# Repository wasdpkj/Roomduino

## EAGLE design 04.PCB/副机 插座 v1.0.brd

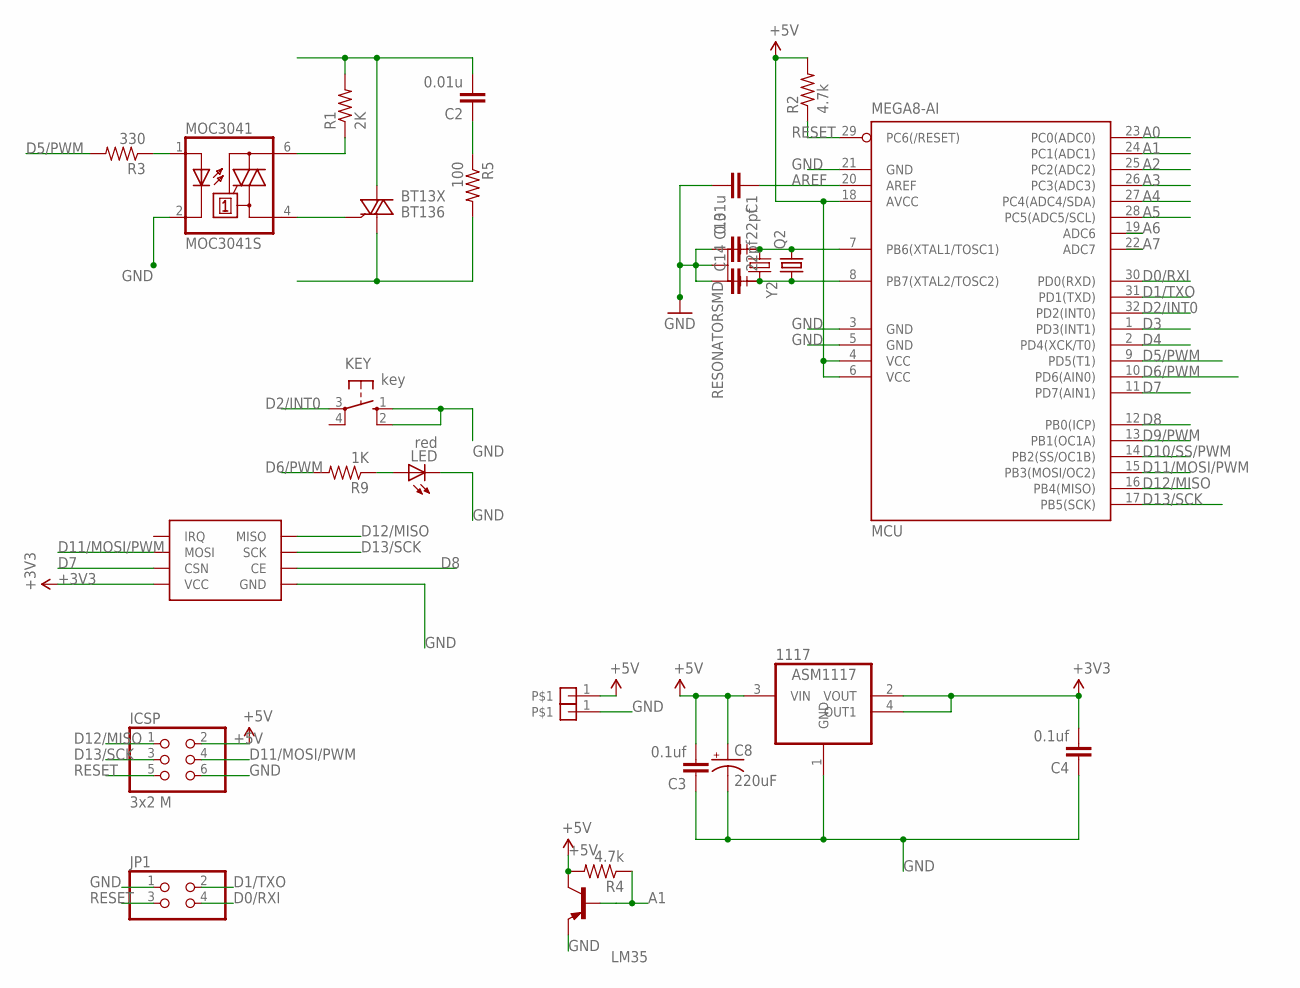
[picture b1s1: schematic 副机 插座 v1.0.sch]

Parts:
1117: ASM1117; SOT223
BT13X: BT136; TO252
C1: 0.01u; 0603-CAP
C2: 0.01u; C050-024X044
C3, C4: 0.1uf; 0603-CAP
C8: 220uF; EIA3528
C13, C14: 22pf; 0603-CAP
ICSP: 3x2 M; 2X03
JP1: PINHD-2X2; 2X02
KEY: key; B3F-10XX; MPN B3F-1000
LED: red; LED3MM
LM35: -PNP-TO92-E1; TO92-E1
MCU: MEGA8-AI; TQFP32-08
MOC3041: MOC3041S; DIL6-SMD; MPN MOC3041S-M
Q2: CRYSTALHC49S; HC49/S
R1: 2K; AXIAL-0.3
R2, R4: 4.7k; 0603-RES
R3: 330; 0603-RES
R5: 100; AXIAL-0.3
R9: 1K; 0603-RES
U$3, U$4: PIN1
U$6: NRF
Y2: RESONATORSMD; RESONATOR-SMD

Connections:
+3V3: 1117.2 (VOUT), 1117.4 (OUT1), C4.2, U$6.P$2 (VCC)
+5V: 1117.3 (VIN), C3.2, C8.A (+), ICSP.2, LM35.1 (C), MCU.4 (VCC), MCU.6 (VCC), MCU.18 (AVCC), R2.2, R4.2, U$3.1
A0: MCU.23 (PC0(ADC0))
A1: LM35.2 (B), MCU.24 (PC1(ADC1)), R4.1
A2: MCU.25 (PC2(ADC2))
A3: MCU.26 (PC3(ADC3))
A4: MCU.27 (PC4(ADC4/SDA))
A5: MCU.28 (PC5(ADC5/SCL))
A6: MCU.19 (ADC6)
A7: MCU.22 (ADC7)
AREF: C1.1, MCU.20 (AREF)
D0/RXI: JP1.4, MCU.30 (PD0(RXD))
D1/TXO: JP1.2, MCU.31 (PD1(TXD))
D2/INT0: KEY.3, MCU.32 (PD2(INT0))
D3: MCU.1 (PD3(INT1))
D4: MCU.2 (PD4(XCK/T0))
D5/PWM: MCU.9 (PD5(T1)), R3.2
D6/PWM: MCU.10 (PD6(AIN0)), R9.2
D7: MCU.11 (PD7(AIN1)), U$6.P$4 (CSN)
D8: MCU.12 (PB0(ICP)), U$6.P$3 (CE)
D9/PWM: MCU.13 (PB1(OC1A))
D10/SS/PWM: MCU.14 (PB2(SS/OC1B))
D11/MOSI/PWM: ICSP.4, MCU.15 (PB3(MOSI/OC2)), U$6.P$6 (MOSI)
D12/MISO: ICSP.1, MCU.16 (PB4(MISO)), U$6.P$7 (MISO)
D13/SCK: ICSP.3, MCU.17 (PB5(SCK)), U$6.P$5 (SCK)
GND: 1117.1 (GND), C1.2, C3.1, C4.1, C8.C (-), C13.1, C14.1, ICSP.6, JP1.1, KEY.1 (S), KEY.2 (S1), LED.K (C), LM35.3 (E), MCU.3 (GND), MCU.5 (GND), MCU.21 (GND), MOC3041.2 (C), U$4.1, U$6.P$1 (GND), Y2.2
IN: BT13X.3 (A2), C2.2, R1.P$2 (2)
unnamed: MOC3041.6 (A2), R1.P$1 (1)
unnamed: BT13X.2 (G), MOC3041.4 (A1)
unnamed: C2.1, R5.P$1 (1)
unnamed: LED.A, R9.1
unnamed: C13.2, MCU.7 (PB6(XTAL1/TOSC1)), Q2.2, Y2.1
unnamed: C14.2, MCU.8 (PB7(XTAL2/TOSC2)), Q2.1, Y2.3
OUT: BT13X.1 (A1), R5.P$2 (2)
P1: MOC3041.1 (A), R3.1
RESET: ICSP.5, JP1.3, MCU.29 (PC6(/RESET)), R2.1

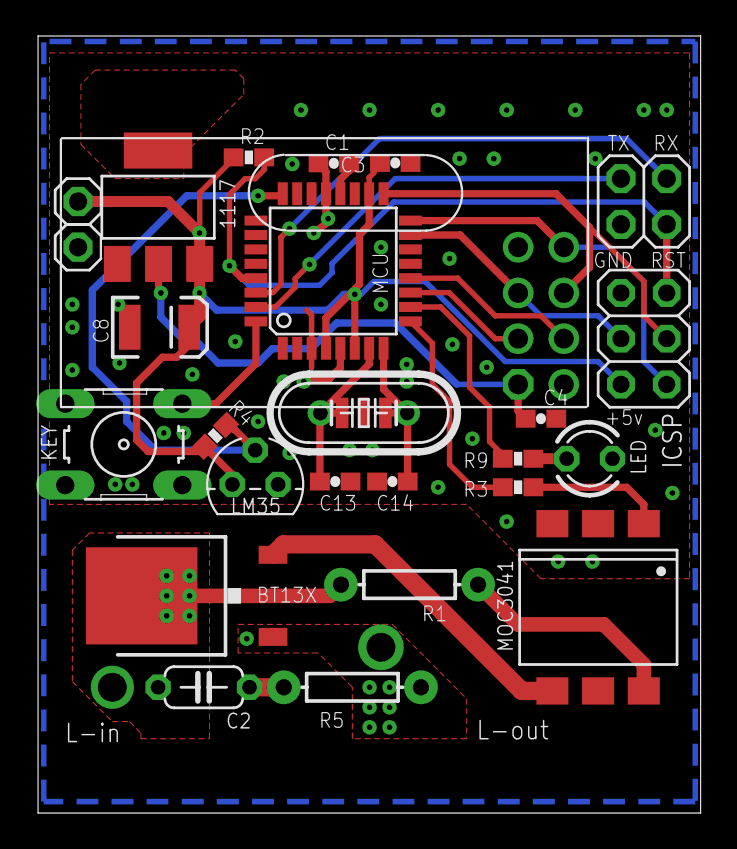
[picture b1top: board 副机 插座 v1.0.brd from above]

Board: 2 copper layers, 36.8 x 43.2 mm, 27 parts (0 on the bottom side), 25 nets.

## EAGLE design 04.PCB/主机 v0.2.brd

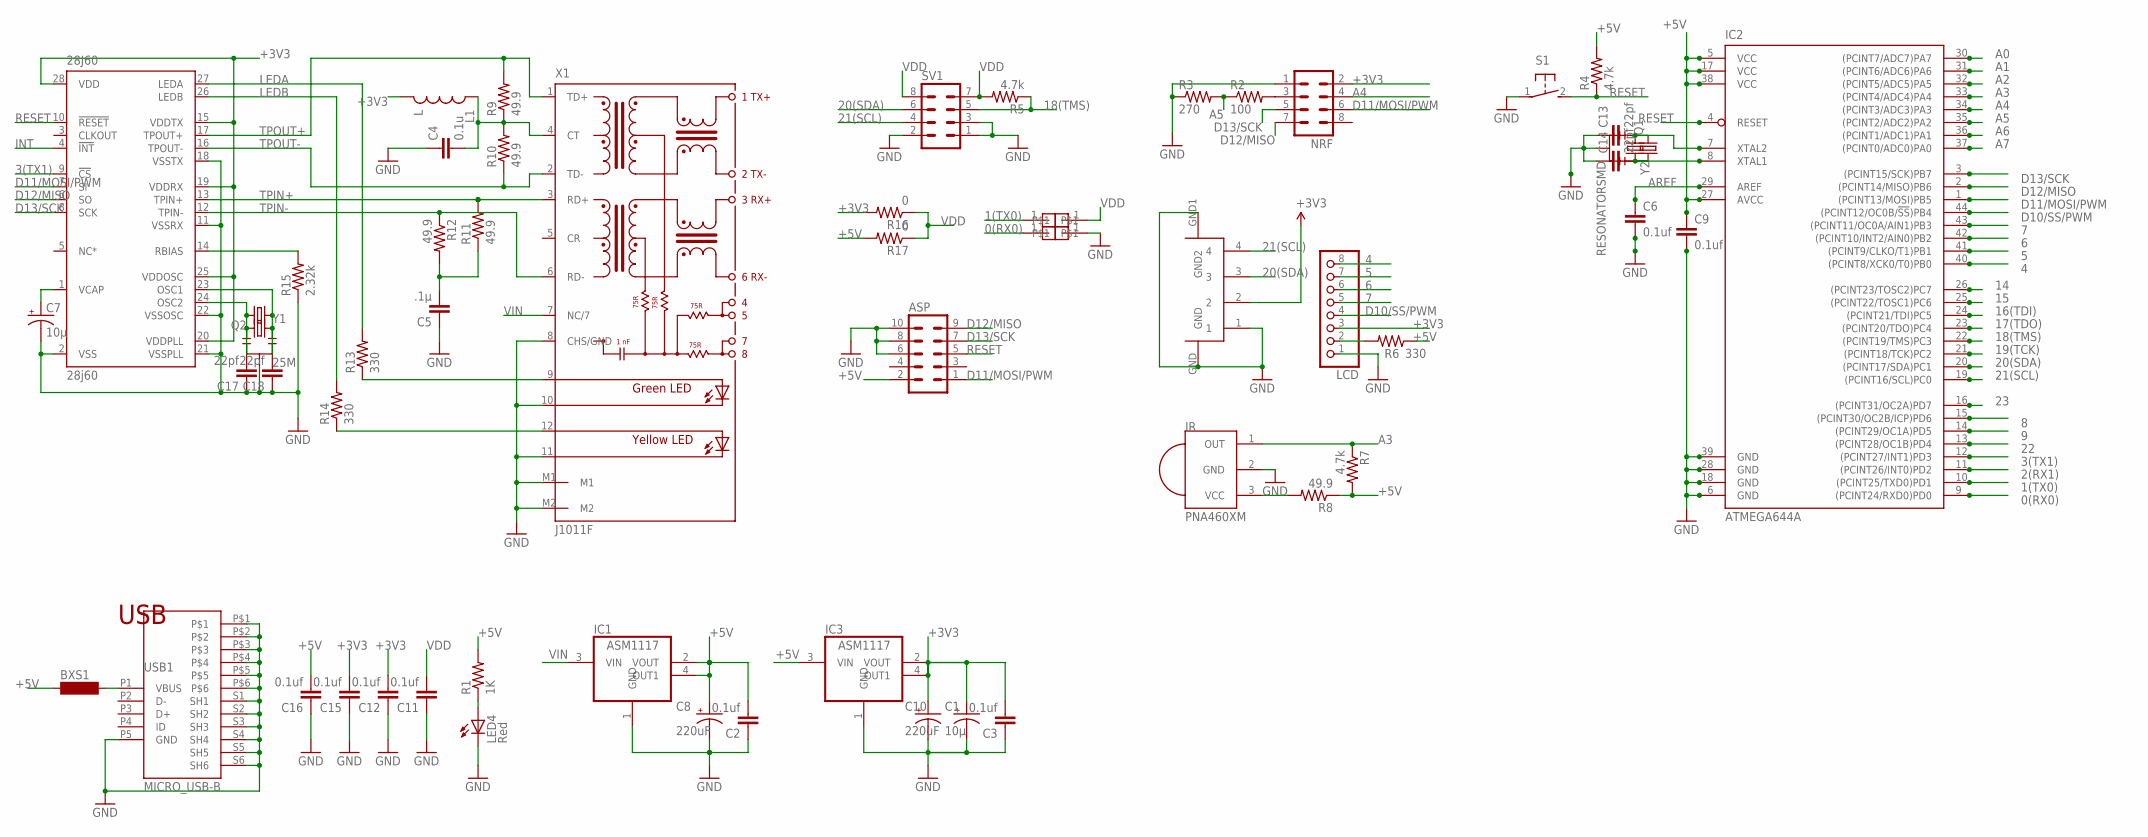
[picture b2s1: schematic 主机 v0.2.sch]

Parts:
28J60: 28j60; SSOP28DB
ASP: MA05-2
BXS1: SM-1206
C1, C7: 10µ; EIA3528
C2, C3, C6, C9, C11, C12, C15, C16: 0.1uf; 0603-CAP
C4: 0.1u; 0603-CAP
C5: .1µ; 0603-CAP
C8, C10: 220uF; 153CLV-0605
C13, C14, C17, C18: 22pf; 0603-CAP
IC1: ASM1117; SOT223
IC2: ATMEGA644A; TQFP44
IC3: ASM1117; SOT223; MPN REG1117
IR: PNA460XM
L1: L; 0603
LCD: PINHD-1X8; 1X08
LED4: Red; 0805-LED
NRF: MA04-2
Q1, Q2: CRYSTALHC49S; HC49/S
R1: 1K; 0603-RES
R2: 100; 0603-RES
R3: 270; 0603-RES
R4, R5, R7: 4.7k; 0603-RES
R6, R13, R14: 330; 0603-RES
R8, R9, R10, R11, R12: 49.9; 0603-RES
R15: 2.32k; 0603-RES
R16, R17: 0; 0603-RES
S1: 31-XX; B3F-31XX
SV1: MA04-2
U$2: S4B-XH-SM4-TB; XH-SM4-TB
U$4, U$5, U$6, U$7: PIN1
USB1: MICRO_USB-B; USB_MICRO_B
X1: J1011F; HRJ
Y1: 25M; RESONATOR-SMD
Y2: RESONATORSMD; RESONATOR-SMD

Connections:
0(RX0): IC2.9 ((PCINT24/RXD0)PD0), U$7.1
1(TX0): IC2.10 ((PCINT25/TXD0)PD1), U$6.1
2(RX1): IC2.11 ((PCINT26/INT0)PD2)
3(TX1): 28J60.9 (!CS), IC2.12 ((PCINT27/INT1)PD3)
4: IC2.40 ((PCINT8/XCK0/T0)PB0), LCD.8
5: IC2.41 ((PCINT9/CLKO/T1)PB1), LCD.7
6: IC2.42 ((PCINT10/INT2/AIN0)PB2), LCD.6
7: IC2.43 ((PCINT11/OC0A/AIN1)PB3), LCD.5
8: IC2.15 ((PCINT30/OC2B/ICP)PD6)
9: IC2.14 ((PCINT29/OC1A)PD5)
14: IC2.26 ((PCINT23/TOSC2)PC7)
15: IC2.25 ((PCINT22/TOSC1)PC6)
16(TDI): IC2.24 ((PCINT21/TDI)PC5)
17(TDO): IC2.23 ((PCINT20/TDO)PC4)
18(TMS): IC2.22 ((PCINT19/TMS)PC3), R5.1, SV1.5
19(TCK): IC2.21 ((PCINT18/TCK)PC2)
20(SDA): IC2.20 ((PCINT17/SDA)PC1), SV1.6, U$2.3
21(SCL): IC2.19 ((PCINT16/SCL)PC0), SV1.4, U$2.4
22: IC2.13 ((PCINT28/OC1B)PD4)
23: IC2.16 ((PCINT31/OC2A)PD7)
+3V3: 28J60.15 (VDDTX), 28J60.19 (VDDRX), 28J60.20 (VDDPLL), 28J60.25 (VDDOSC), 28J60.28 (VDD), C1.A (+), C3.2, C10.+, C12.2, C15.2, IC3.2 (VOUT), IC3.4 (OUT1), L1.2, LCD.3, NRF.2, R16.2, U$2.2
+5V: ASP.2, BXS1.1, C2.2, C8.+, C9.1, C16.2, IC1.2 (VOUT), IC1.4 (OUT1), IC2.5 (VCC), IC2.17 (VCC), IC2.27 (AVCC), IC2.38 (VCC), IC3.3 (VIN), R1.2, R4.2, R6.1, R7.2, R8.1, R17.2
A0: IC2.30 ((PCINT7/ADC7)PA7)
A1: IC2.31 ((PCINT6/ADC6)PA6)
A2: IC2.32 ((PCINT5/ADC5)PA5)
A3: IC2.33 ((PCINT4/ADC4)PA4), IR.1 (OUT), R7.1
A4: IC2.34 ((PCINT3/ADC3)PA3), NRF.4
A5: IC2.35 ((PCINT2/ADC2)PA2), R2.1, R3.2
A6: IC2.36 ((PCINT1/ADC1)PA1)
A7: IC2.37 ((PCINT0/ADC0)PA0)
AREF: C6.1, IC2.29 (AREF)
D10/SS/PWM: IC2.44 ((PCINT12/OC0B/!SS!)PB4), LCD.4
D11/MOSI/PWM: 28J60.7 (SI), ASP.1, IC2.1 ((PCINT13/MOSI)PB5), NRF.6
D12/MISO: 28J60.6 (SO), ASP.9, IC2.2 ((PCINT14/MISO)PB6), NRF.7
D13/SCK: 28J60.8 (SCK), ASP.7, IC2.3 ((PCINT15/SCK)PB7), NRF.5
GND: 28J60.2 (VSS), 28J60.11 (VSSRX), 28J60.18 (VSSTX), 28J60.21 (VSSPLL), 28J60.22 (VSSOSC), ASP.6, ASP.8, ASP.10, C1.C (-), C2.1, C3.1, C4.1, C5.1, C6.2, C7.C (-), C8.-, C9.2, C10.-, C11.1, C12.1, C13.1, C14.1, C15.1, C16.1, C17.1, C18.1, IC1.1 (GND), IC2.6 (GND), IC2.18 (GND), IC2.28 (GND), IC2.39 (GND), IC3.1 (GND), IR.2 (GND), LCD.1, LED4.C, NRF.1, R3.1, R15.1, S1.1, SV1.1, SV1.2, SV1.3, U$2.1, U$2.GND, U$2.GND1 (GND2), U$4.1, USB1.P5 (GND), USB1.P$1, USB1.P$2, USB1.P$3, USB1.P$4, USB1.P$5, USB1.P$6, USB1.S1 (SH1), USB1.S2 (SH2), USB1.S3 (SH3), USB1.S4 (SH4), USB1.S5 (SH5), USB1.S6 (SH6), X1.8 (CHS/GND), X1.10 (C-R), X1.11 (C-L), X1.M1, X1.M2, Y1.2, Y2.2
INT: 28J60.4 (!INT)
LEDA: 28J60.27 (LEDA), R13.2
LEDB: 28J60.26 (LEDB), R14.2
unnamed: C13.2, IC2.7 (XTAL2), Q1.2, Y2.1
unnamed: IR.3 (VCC), R8.2
unnamed: LED4.A, R1.1
unnamed: NRF.3, R2.2
unnamed: C5.2, R11.1, R12.2
unnamed: 28J60.1 (VCAP), C7.A (+)
unnamed: 28J60.14 (RBIAS), R15.2
unnamed: C14.2, IC2.8 (XTAL1), Q1.1, Y2.3
unnamed: C4.2, L1.1, R9.1, R10.2, X1.4 (CT)
unnamed: 28J60.24 (OSC2), C17.2, Q2.2, Y1.1
unnamed: 28J60.23 (OSC1), C18.2, Q2.1, Y1.3
unnamed: R13.1, X1.9 (A-R)
unnamed: R14.1, X1.12 (AL)
unnamed: LCD.2, R6.2
RESET: 28J60.10 (!RESET), ASP.5, IC2.4 (RESET), R4.1, S1.2 (S)
TPIN+: 28J60.13 (TPIN+), R11.2, X1.3 (RD+)
TPIN-: 28J60.12 (TPIN-), R12.1, X1.6 (RD-)
TPOUT+: 28J60.17 (TPOUT+), R9.2, X1.1 (TD+)
TPOUT-: 28J60.16 (TPOUT-), R10.1, X1.2 (TD-)
VDD: C11.2, R5.2, R16.1, R17.1, SV1.7, SV1.8, U$5.1
VIN: IC1.3 (VIN), X1.7 (NC/7)
VUSB: BXS1.2, USB1.P1 (VBUS)

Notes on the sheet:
USB

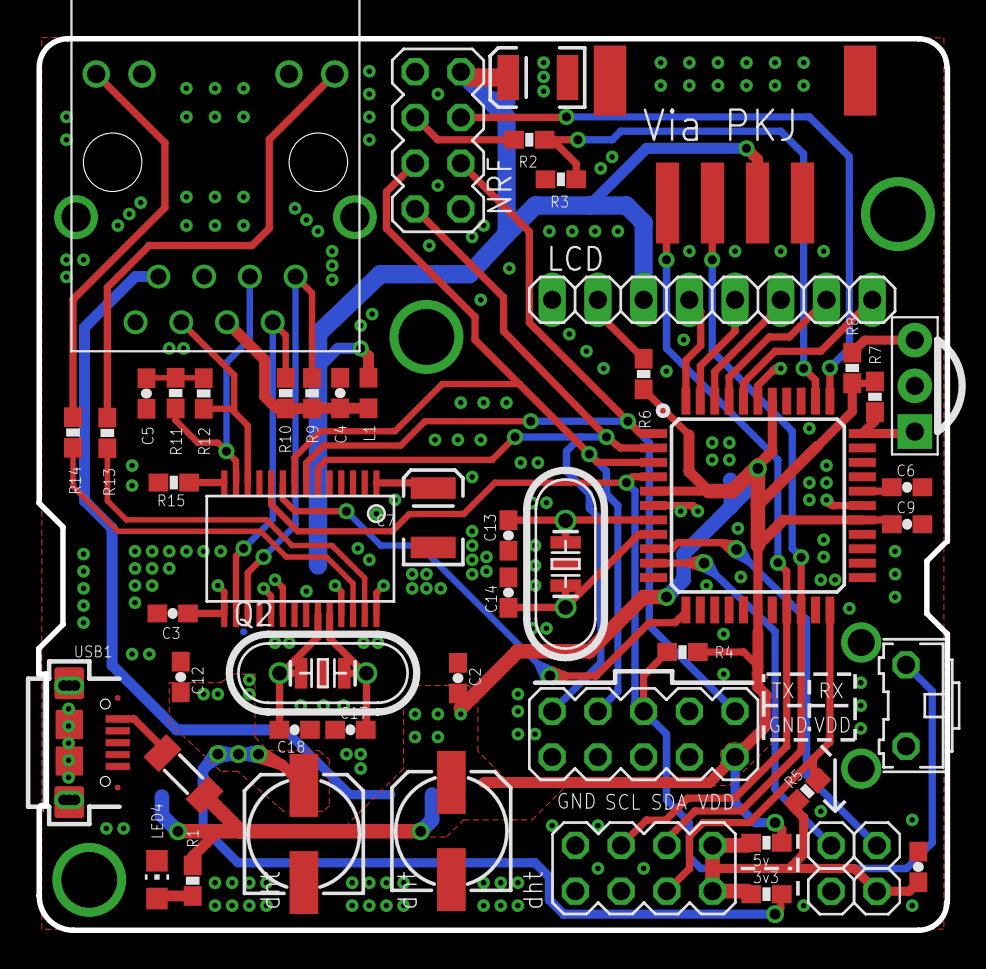
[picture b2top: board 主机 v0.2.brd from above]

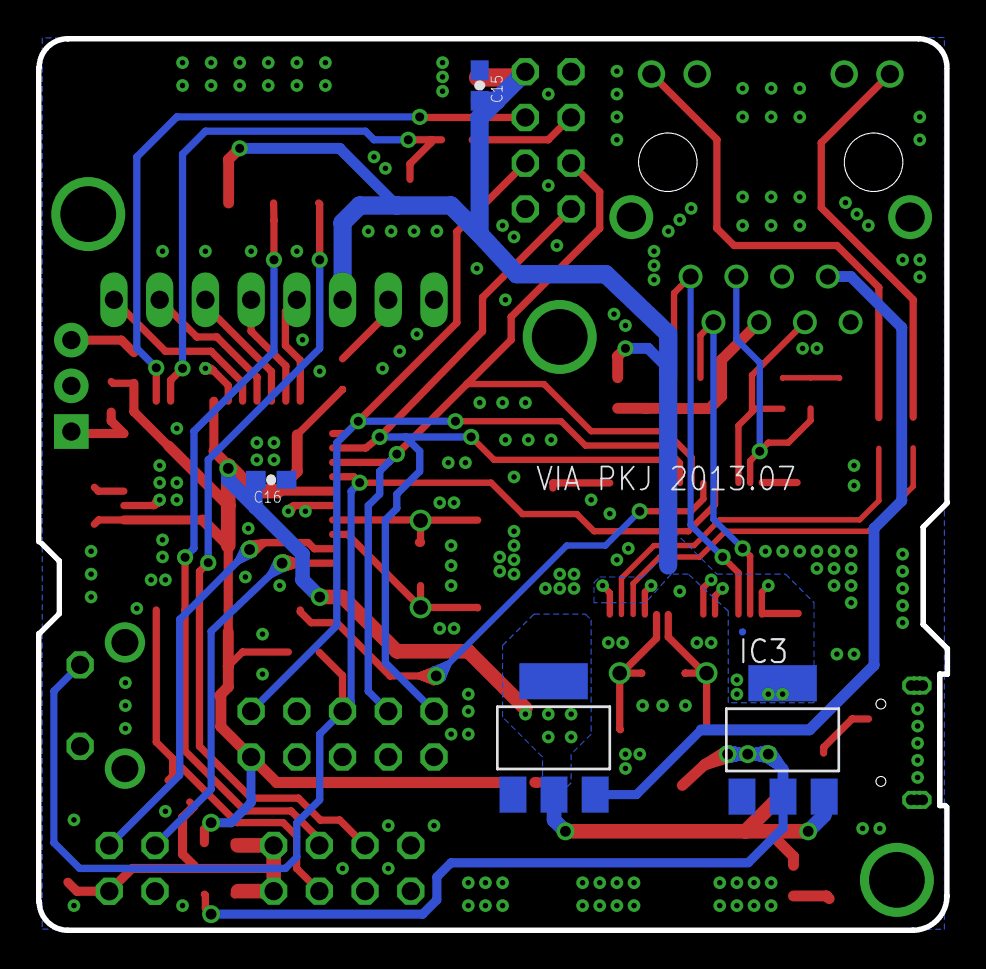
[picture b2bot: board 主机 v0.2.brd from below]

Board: 2 copper layers, 50.5 x 49.5 mm, 59 parts (4 on the bottom side), 45 nets.

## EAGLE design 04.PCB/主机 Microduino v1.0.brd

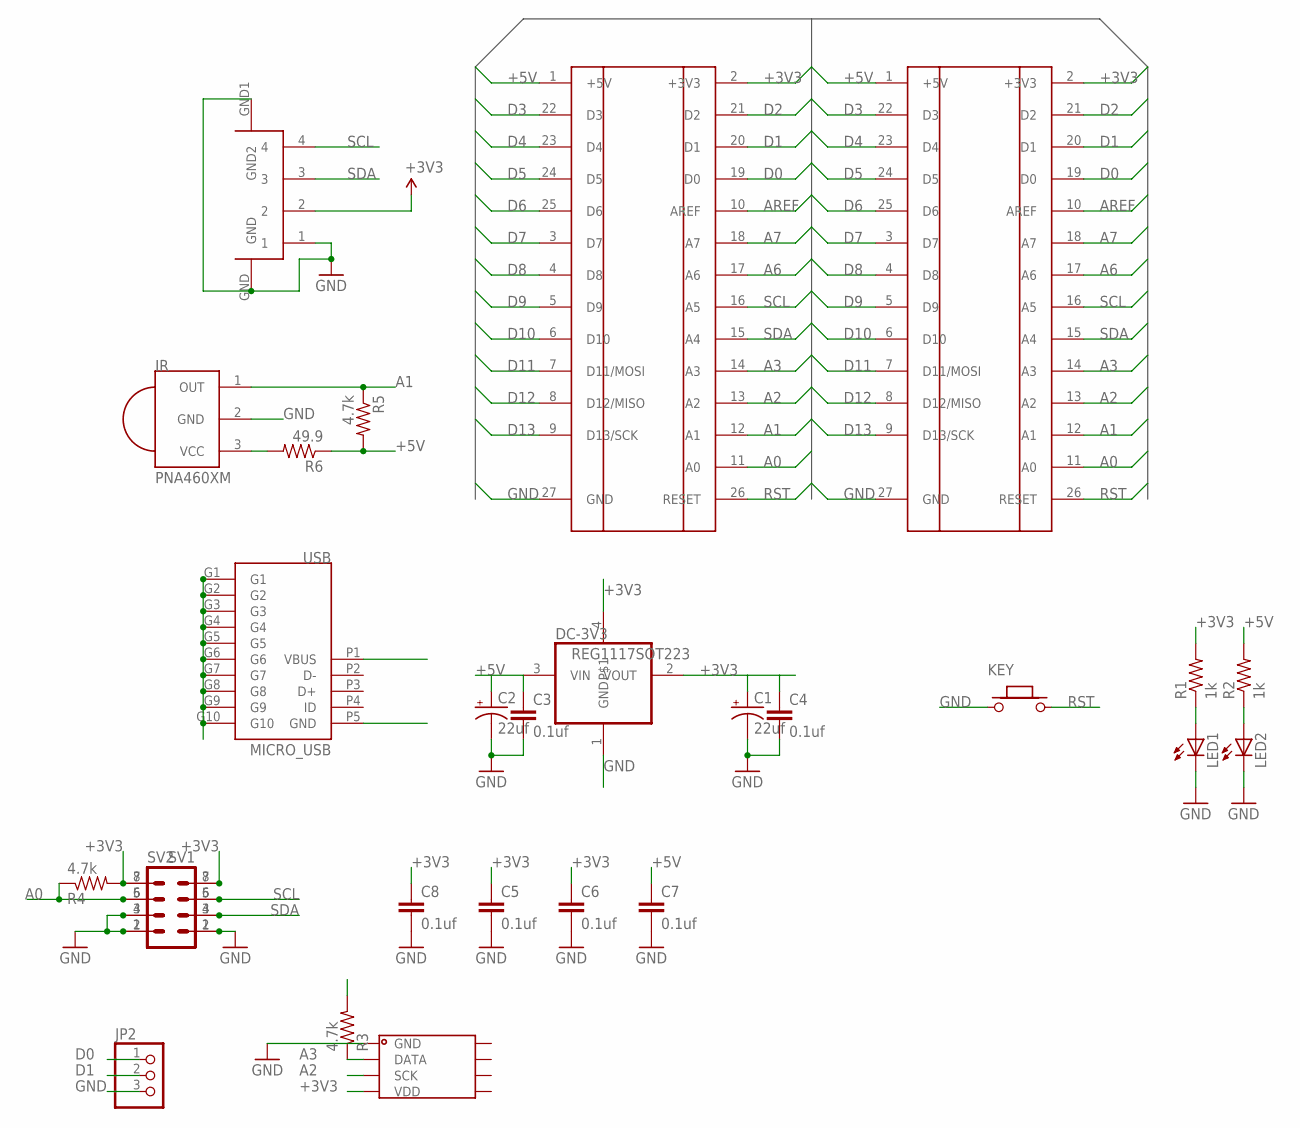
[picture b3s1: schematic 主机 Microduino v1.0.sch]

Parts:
C1, C2: 22uf; EIA3216
C3, C4, C5, C6, C7, C8: 0.1uf; 0603-CAP
DC-3V3: REG1117SOT223; SOT223
IR: PNA460XM
JP2: PINHD-1X3; 1X03
KEY: KEY-TES-018; KEY-TS-018
LED1, LED2: LED0805; 0805-LED
R1, R2: 1k; 0603-RES
R3, R4, R5: 4.7k; 0603-RES
R6: 49.9; 0603-RES
SV1, SV2: MA04-2
U$1, U$2: PING-MICRDUINO/1009+; PIN-MICRODUINO-1009
U$3: S4B-XH-SM4-TB; XH-SM4-TB
U$4: SHT11
USB: MICRO_USB; MICRO_USB_LJ

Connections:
+3V3: C1.A (+), C4.1, C5.1, C6.1, C8.1, DC-3V3.2 (VOUT), DC-3V3.4, R1.2, R3.2, R4.2, SV1.7, SV1.8, SV2.7, SV2.8, U$1.2 (+3V3), U$2.2 (+3V3), U$3.2, U$4.4 (VDD)
+5V: C2.A (+), C3.1, C7.1, DC-3V3.3 (VIN), R2.2, R5.2, R6.1, U$1.1 (+5V), U$2.1 (+5V), USB.P1 (VBUS)
A0: R4.1, SV1.5, SV2.6, U$1.11 (A0), U$2.11 (A0)
A1: IR.1 (OUT), R5.1, U$1.12 (A1), U$2.12 (A1)
A2: U$1.13 (A2), U$2.13 (A2), U$4.3 (SCK)
A3: R3.1, U$1.14 (A3), U$2.14 (A3), U$4.2 (DATA)
A6: U$1.17 (A6), U$2.17 (A6)
A7: U$1.18 (A7), U$2.18 (A7)
AREF: U$1.10 (AREF), U$2.10 (AREF)
D0: JP2.1, U$1.19 (D0), U$2.19 (D0)
D1: JP2.2, U$1.20 (D1), U$2.20 (D1)
D2: U$1.21 (D2), U$2.21 (D2)
D3: U$1.22 (D3), U$2.22 (D3)
D4: U$1.23 (D4), U$2.23 (D4)
D5: U$1.24 (D5), U$2.24 (D5)
D6: U$1.25 (D6), U$2.25 (D6)
D7: U$1.3 (D7), U$2.3 (D7)
D8: U$1.4 (D8), U$2.4 (D8)
D9: U$1.5 (D9), U$2.5 (D9)
D10: U$1.6 (D10), U$2.6 (D10)
D11: U$1.7 (D11/MOSI), U$2.7 (D11/MOSI)
D12: U$1.8 (D12/MISO), U$2.8 (D12/MISO)
D13: U$1.9 (D13/SCK), U$2.9 (D13/SCK)
GND: C1.C (-), C2.C (-), C3.2, C4.2, C5.2, C6.2, C7.2, C8.2, DC-3V3.1 (GND), IR.2 (GND), JP2.3, KEY.2 (1), LED1.C, LED2.C, SV1.1, SV1.2, SV1.3, SV2.1, SV2.2, SV2.4, U$1.27 (GND), U$2.27 (GND), U$3.1, U$3.GND, U$3.GND1 (GND2), U$4.1 (GND), USB.G1, USB.G2, USB.G3, USB.G4, USB.G5, USB.G6, USB.G7, USB.G8, USB.G9, USB.G10, USB.P5 (GND)
unnamed: IR.3 (VCC), R6.2
unnamed: LED1.A, R1.1
unnamed: LED2.A, R2.1
RST: KEY.1 (2), U$1.26 (RESET), U$2.26 (RESET)
SCL: SV1.6, SV2.5, U$1.16 (A5), U$2.16 (A5), U$3.4
SDA: SV1.4, SV2.3, U$1.15 (A4), U$2.15 (A4), U$3.3

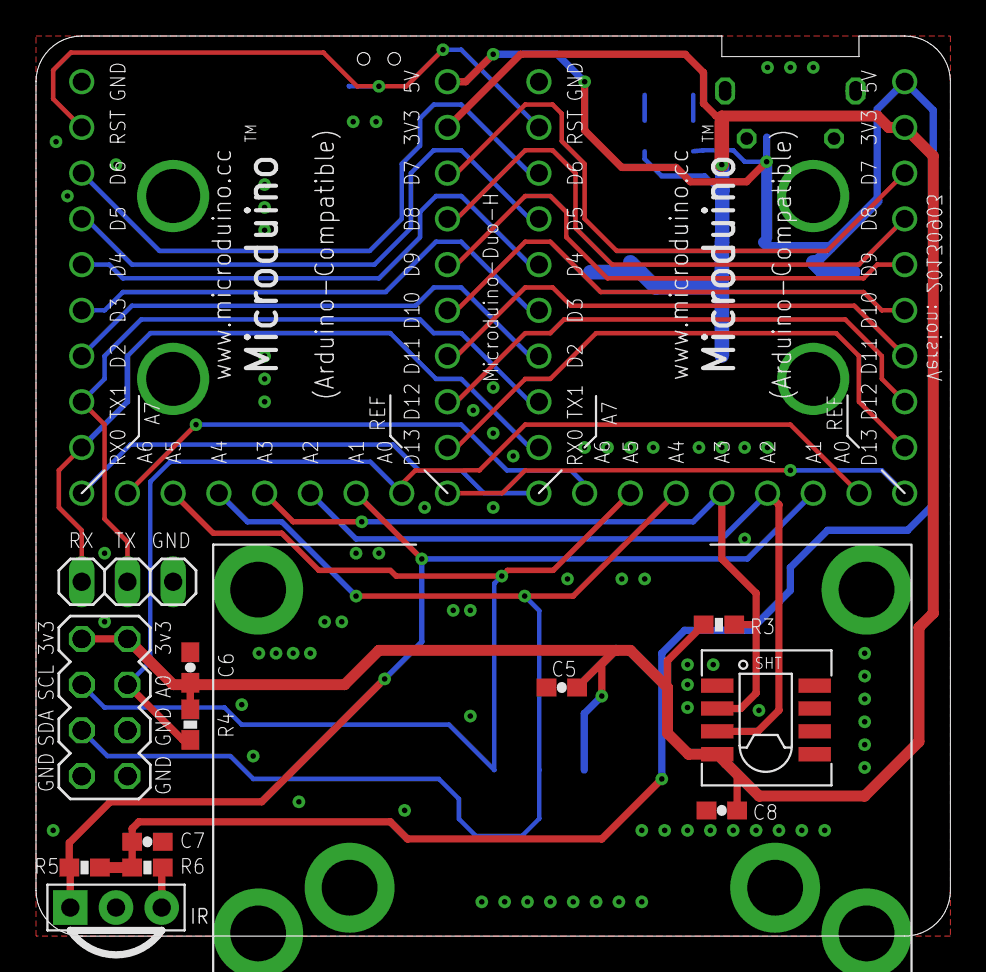
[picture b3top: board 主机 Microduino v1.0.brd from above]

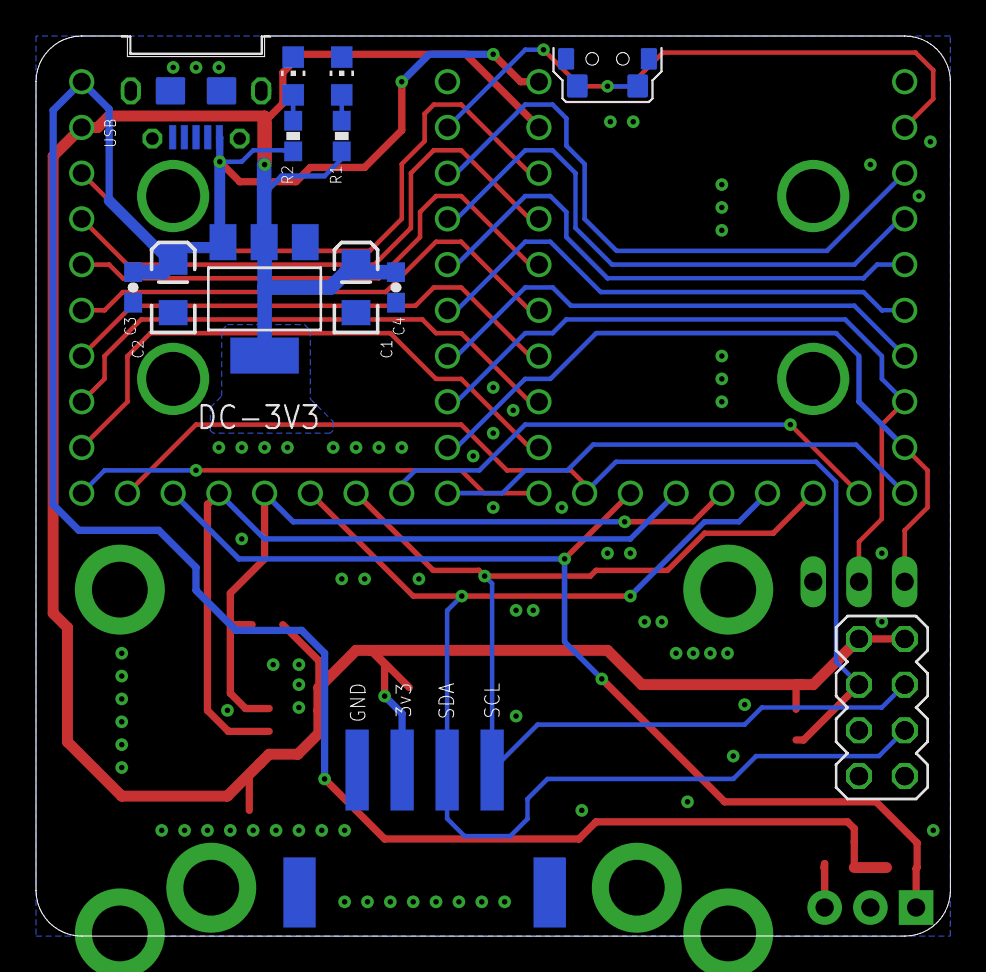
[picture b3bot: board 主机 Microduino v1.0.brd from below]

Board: 2 copper layers, 50.8 x 50.0 mm, 27 parts (15 on the bottom side), 30 nets.

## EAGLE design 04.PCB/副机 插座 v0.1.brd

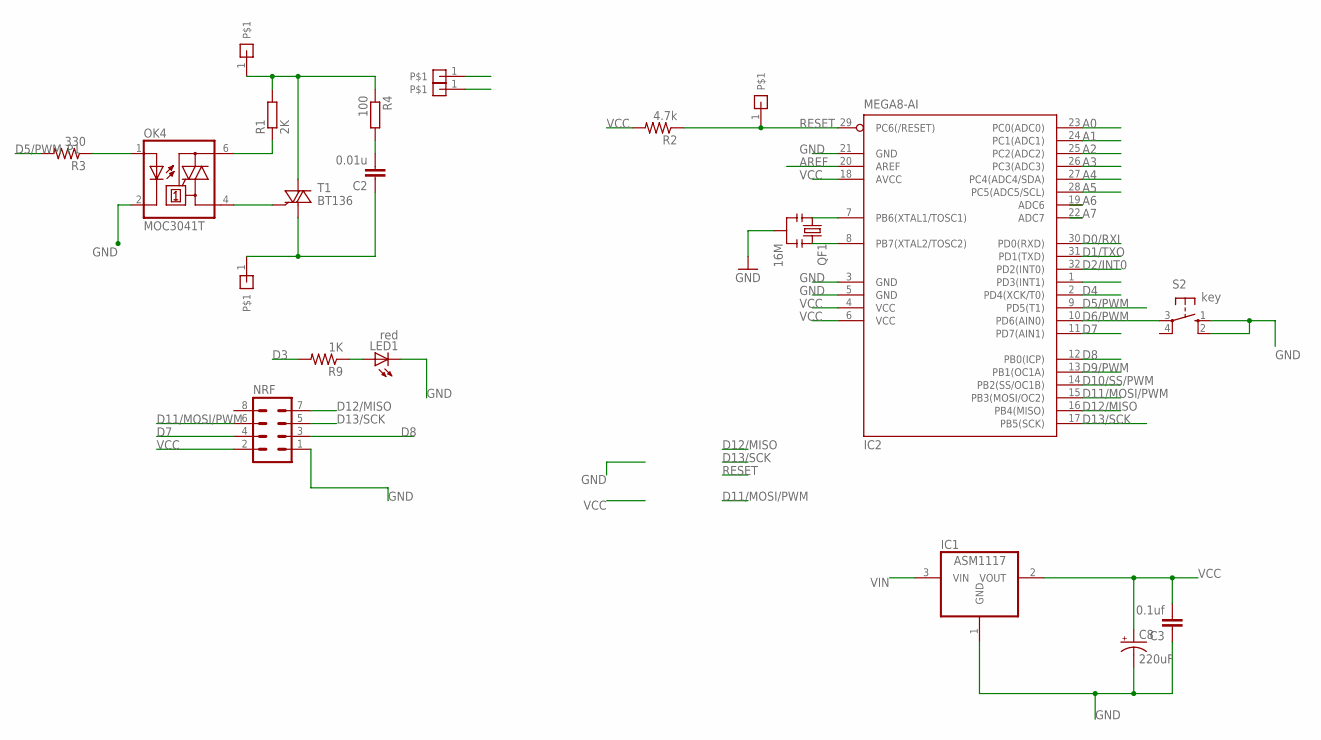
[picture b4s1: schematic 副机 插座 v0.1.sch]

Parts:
C2: 0.01u; C050-024X044
C3: 0.1uf; 0603-CAP
C8: 220uF; EIA3528
IC1: ASM1117; SOT223
IC2: MEGA8-AI; TQFP32-08
LED1: red; LED3MM
NRF: MA04-2
OK4: MOC3041T; DIL06B
QF1: 16M; RESONATOR-PTH
R1: 2K; 0204/7
R2: 4.7k; 0603-RES
R3: 330; 0603-RES
R4: 100; 0204/7
R9: 1K; 0603-RES
S2: key; B3F-10XX; MPN B3F-1000
T1: BT136; TO220AB
U$1, U$2, U$3, U$4, U$5: PIN1

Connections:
A0: IC2.23 (PC0(ADC0))
A1: IC2.24 (PC1(ADC1))
A2: IC2.25 (PC2(ADC2))
A3: IC2.26 (PC3(ADC3))
A4: IC2.27 (PC4(ADC4/SDA))
A5: IC2.28 (PC5(ADC5/SCL))
A6: IC2.19 (ADC6)
A7: IC2.22 (ADC7)
AREF: IC2.20 (AREF)
D0/RXI: IC2.30 (PD0(RXD))
D1/TXO: IC2.31 (PD1(TXD))
D2/INT0: IC2.32 (PD2(INT0))
D3: IC2.1 (PD3(INT1)), R9.2
D4: IC2.2 (PD4(XCK/T0))
D5/PWM: IC2.9 (PD5(T1)), R3.2
D6/PWM: IC2.10 (PD6(AIN0)), S2.3
D7: IC2.11 (PD7(AIN1)), NRF.4
D8: IC2.12 (PB0(ICP)), NRF.3
D9/PWM: IC2.13 (PB1(OC1A))
D10/SS/PWM: IC2.14 (PB2(SS/OC1B))
D11/MOSI/PWM: IC2.15 (PB3(MOSI/OC2)), NRF.6
D12/MISO: IC2.16 (PB4(MISO)), NRF.7
D13/SCK: IC2.17 (PB5(SCK)), NRF.5
GND: C3.1, C8.C (-), IC1.1 (GND), IC2.3 (GND), IC2.5 (GND), IC2.21 (GND), LED1.K (C), NRF.1, OK4.2 (C), QF1.2, S2.1 (S), S2.2 (S1), U$4.1
IN: R1.2, R4.1, T1.2 (A2), U$2.1
unnamed: OK4.6 (A2), R1.1
unnamed: OK4.4 (A1), T1.3 (G)
unnamed: C2.2, R4.2
unnamed: LED1.A, R9.1
OUT: C2.1, T1.1 (A1), U$1.1
P1: OK4.1 (A), R3.1
PB6: IC2.7 (PB6(XTAL1/TOSC1)), QF1.1
PB7: IC2.8 (PB7(XTAL2/TOSC2)), QF1.3
RESET: IC2.29 (PC6(/RESET)), R2.1, U$5.1
VCC: C3.2, C8.A (+), IC1.2 (VOUT), IC2.4 (VCC), IC2.6 (VCC), IC2.18 (AVCC), NRF.2, R2.2
VIN: IC1.3 (VIN), U$3.1

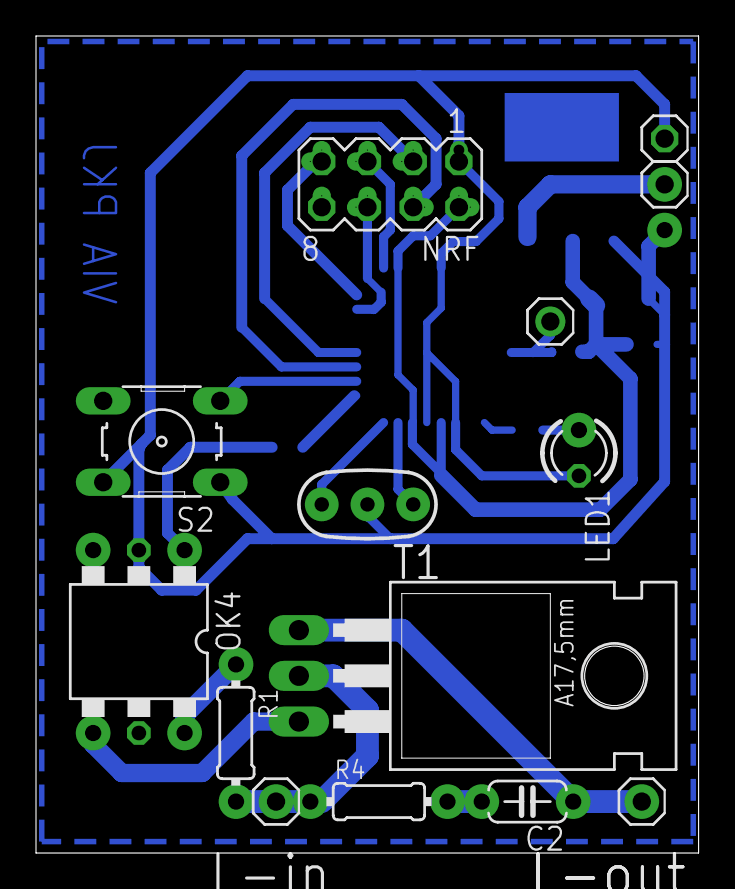
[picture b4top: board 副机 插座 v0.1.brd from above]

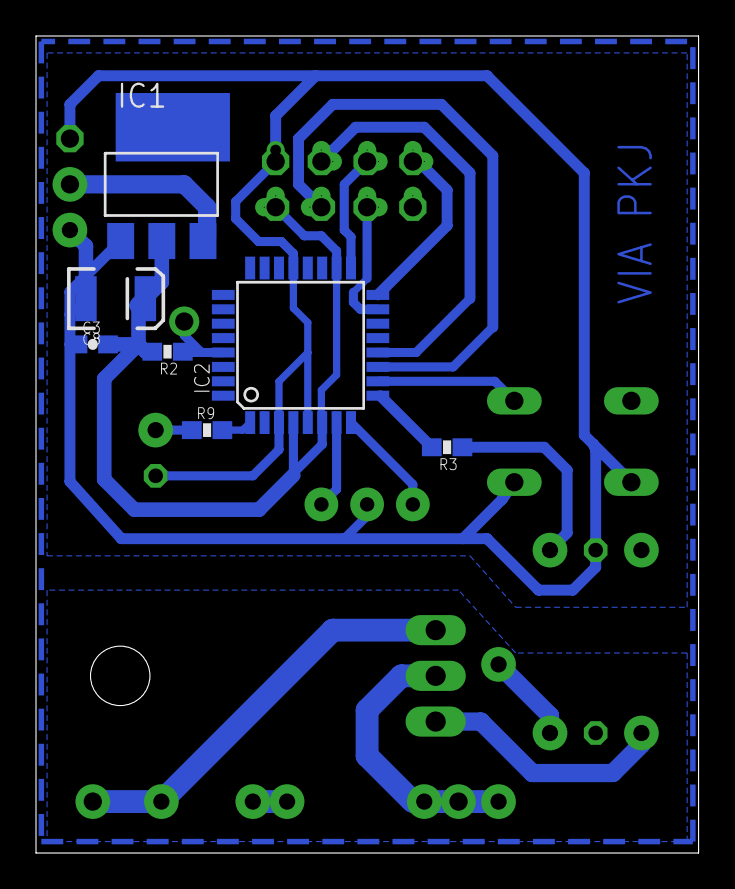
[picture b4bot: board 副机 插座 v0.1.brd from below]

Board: 2 copper layers, 36.8 x 45.4 mm, 21 parts (7 on the bottom side), 21 nets.

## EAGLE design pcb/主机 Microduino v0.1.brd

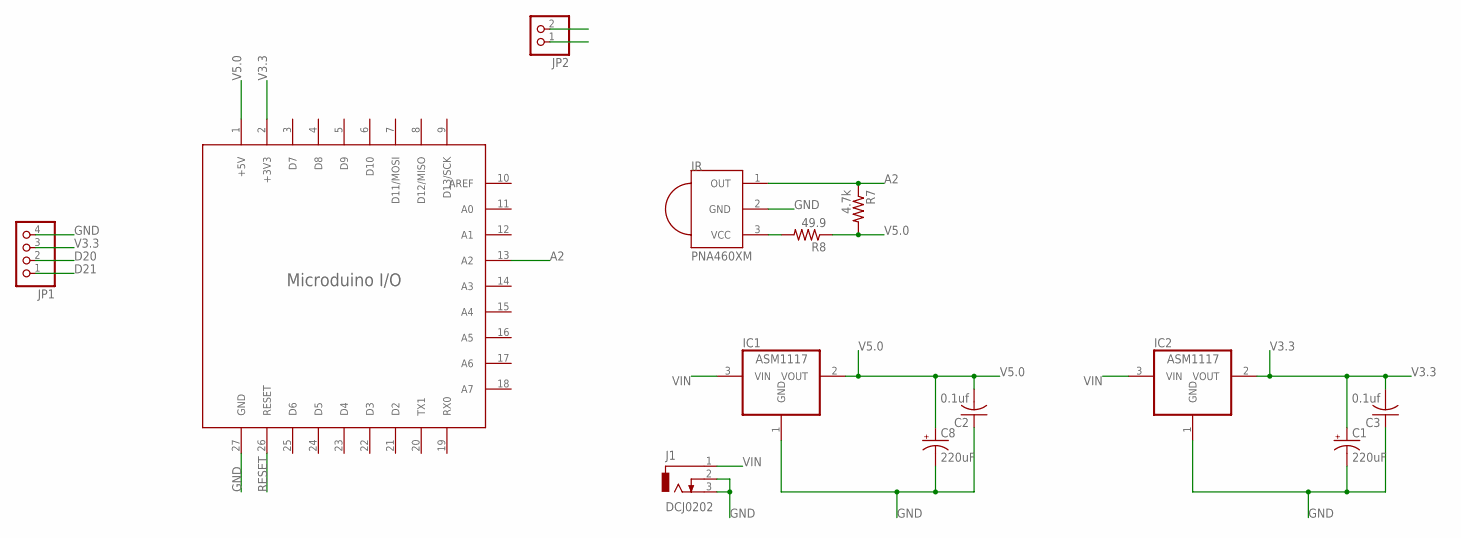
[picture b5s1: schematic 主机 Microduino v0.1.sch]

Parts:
C1, C8: 220uF; E2,5-5
C2, C3: 0.1uf; C025-024X044
IC1, IC2: ASM1117; SOT223
IR: PNA460XM
J1: DCJ0202
JP1: PINHD-1X4; 1X04
JP2: PINHD-1X2; 1X02
R7: 4.7k; AXIAL-0.3
R8: 49.9; AXIAL-0.3
U$1: PING-MICRDUINO-DZ/1009; PIN-MICRODUINO-1009

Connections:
A2: IR.1 (OUT), R7.P$1 (1), U$1.13 (A2)
D20: JP1.2, JP2.2
D21: JP1.1, JP2.1
GND: C1.-, C2.1, C3.1, C8.-, IC1.1 (GND), IC2.1 (GND), IR.2 (GND), J1.2, J1.3, JP1.4, U$1.27 (GND)
unnamed: IR.3 (VCC), R8.P$2 (2)
RESET: U$1.26 (RESET)
V3.3: C1.+, C3.2, IC2.2 (VOUT), IC2.4, JP1.3, U$1.2 (+3V3)
V5.0: C2.2, C8.+, IC1.2 (VOUT), IC1.4, R7.P$2 (2), R8.P$1 (1), U$1.1 (+5V)
VIN: IC1.3 (VIN), IC2.3 (VIN), J1.1

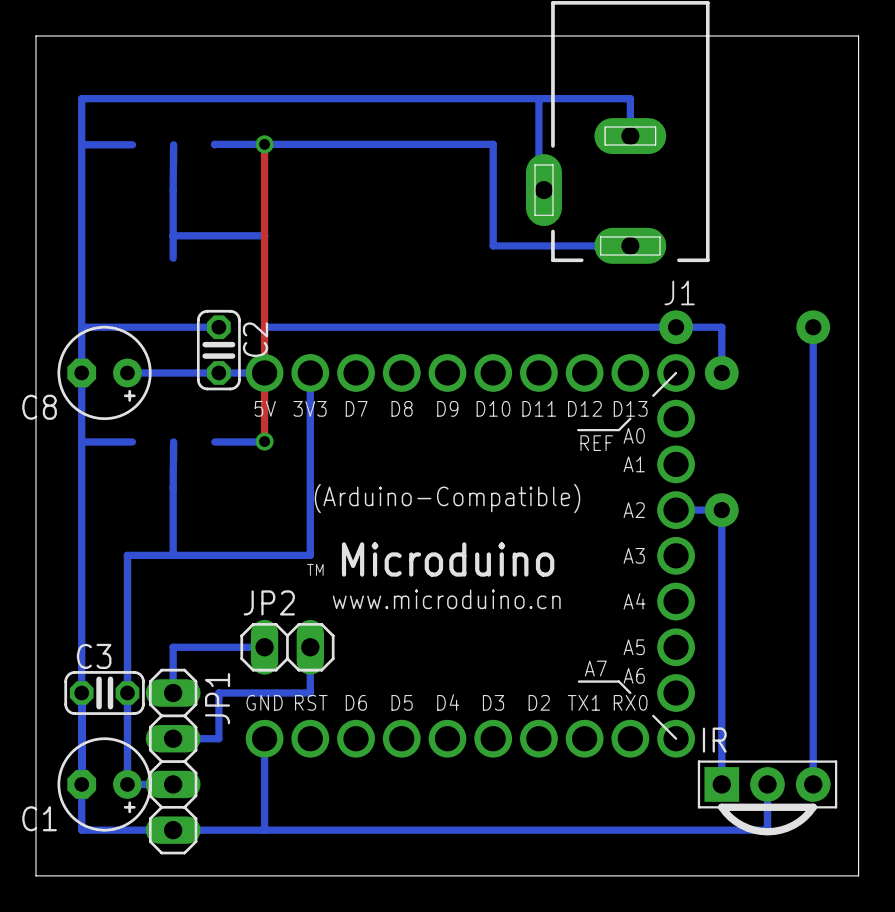
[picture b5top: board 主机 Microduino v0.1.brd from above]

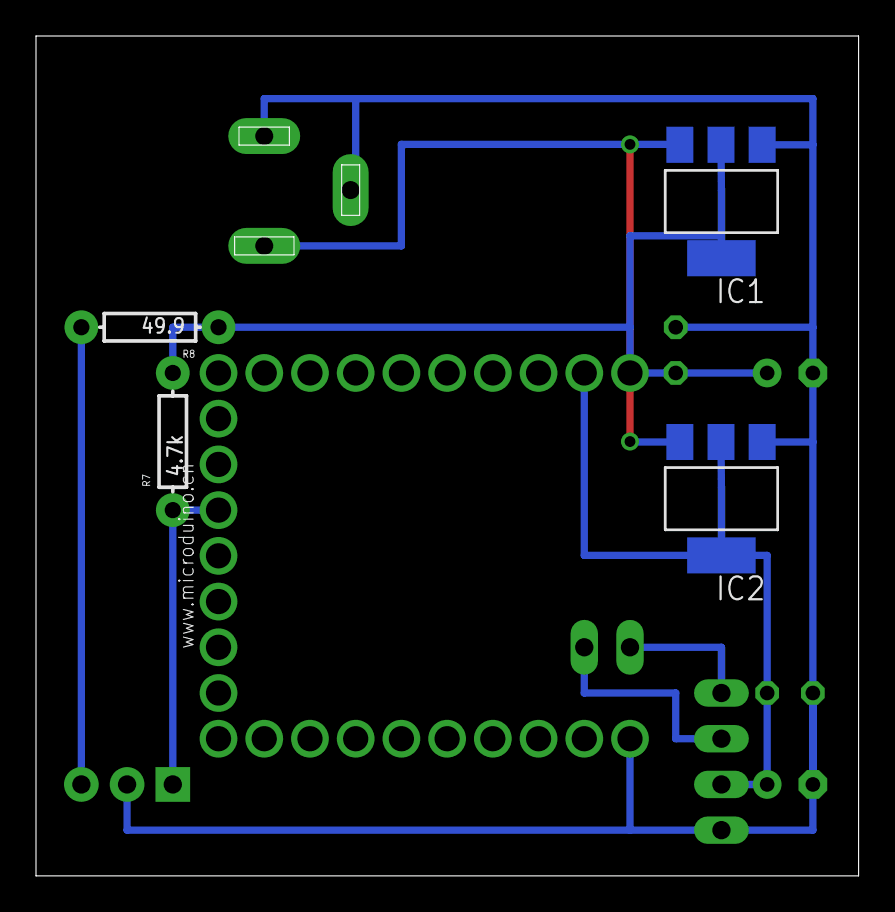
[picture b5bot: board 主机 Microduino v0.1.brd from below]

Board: 2 copper layers, 45.7 x 46.7 mm, 13 parts (5 on the bottom side), 8 nets.
